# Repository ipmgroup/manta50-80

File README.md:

# manta50-80
Motor-Controller, FOC

### Manta50 key characteristics

    DC-Input 4.4V to 45V 
    Maximum DC / AC (per phase) current - 20A
    Texas Instruments C2000 Piccolo TMS320F28027F
    CAN - MCP2515
    Three-Phase Smart Gate Driver - DRV8305
    one GPIO input for PWM(not supported in FW)

with good cooling in water, you can increase the AC current to 80A. Replacing the resistance from 0.007R to 0.002R.

#### [Firmware](https://github.com/ipmgroup/manta50_fw)

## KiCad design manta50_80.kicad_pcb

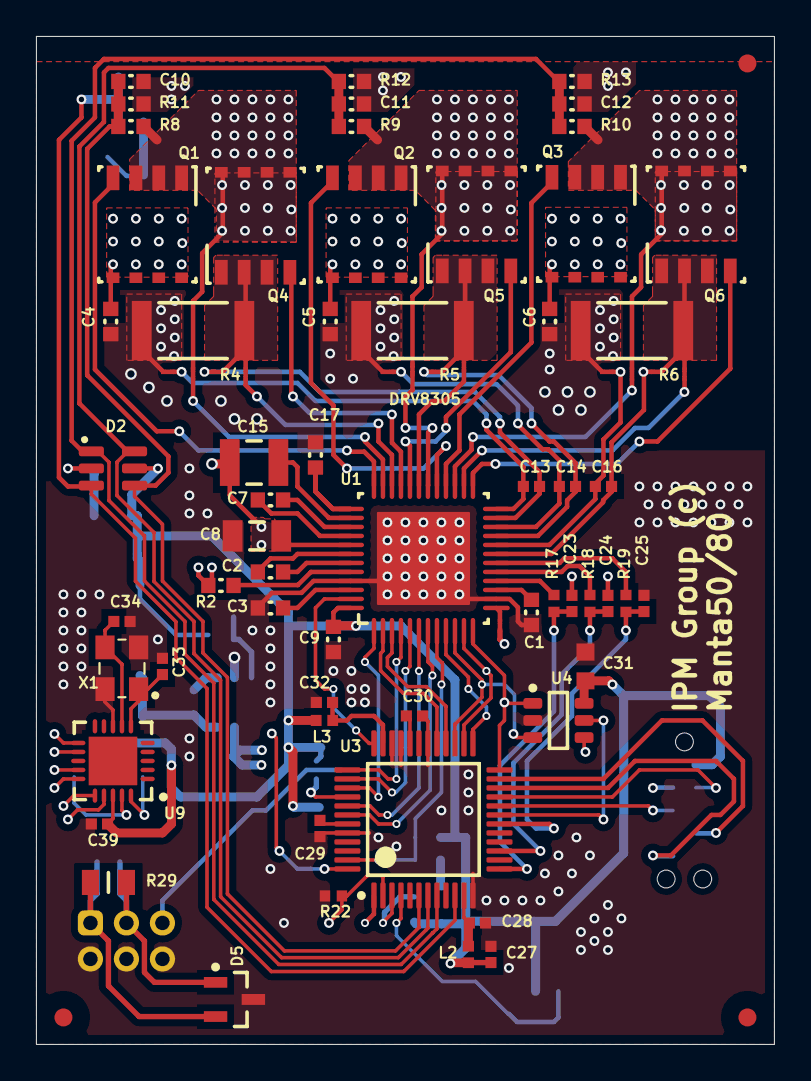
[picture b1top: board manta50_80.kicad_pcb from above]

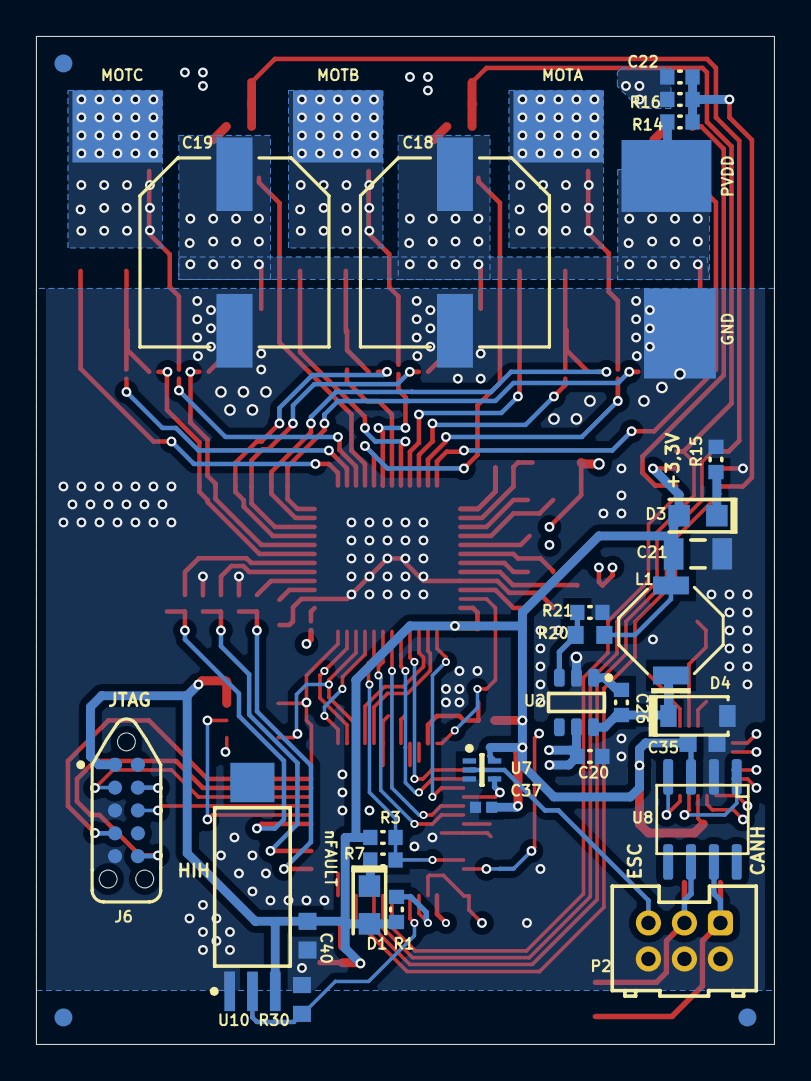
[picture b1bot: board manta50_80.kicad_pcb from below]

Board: 4 copper layers, 41.0 x 56.0 mm, 111 parts (36 on the bottom side), 87 nets.

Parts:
C1, C3, C4, C5, C6, C9, C17, C20: UMK107AB7105KA-T; 0603L
C2, C7: C0603C473K1RACTU; 0603L
C8: GRM31CR71H475KA12L; 1206L
C10, C11, C12, C22: C0603C104J4RACTU; 0603L
C13, C14, C16: 1nF; CAPC1005X55N
C15: GRM32ER72A225KA35L; 1210L
C18, C19: EEE-FT1H331AP; SM_RADIAL_G
C21: GRM31CR71A226KE15L; 1206L
C23, C24, C25: 2.2nF; CAPC1005X55N
C26: GRM188R71C334KA01D; 0603L
C27, C28, C29, C30, C32: 2.2uF; _Users_Public_Documents_Altium_AD15_Library_CernLib_PcbLib_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
C31, C35, C37: 100nF; _Users_Public_Documents_Altium_AD15_Library_CernLib_PcbLib_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
C33, C34: 22pF; CAPC1005X55N
C39: 100nF; CAPC1005X55N
C40: 100nF; _Users_Andrew_Documents_Altium_CernLib_PcbLib_Capacitors SM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
D1: LTST-C170KRKT; LED_LTST-C170
D2: NUP4201MR6T1G; TSOP-6
D3: LTST-C171GKT; LED_LTST-C171
D4: MBR1H100SFT3G; SOD-123FL
D5: SM712; SOT23_N
FID1, FID2, FID3, FID4, FID5, FID6: Fiducial; FIDUCIAL10-20
J1, J2, J3, J4, J5: 2 way net tie junction; J_PIN_4X5
J6: TC2050-IDC-NL-FP; TAG_TC2050-NL
L1: SD53-150-R; SD53
L2: 220R@100MHz; _Users_Public_Documents_Altium_AD15_Library_CernLib_PcbLib_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
L3: 60R@100MHz; _Users_Public_Documents_Altium_AD15_Library_CernLib_PcbLib_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
NT1, NT2, NT3, NT4, NT5, NT6, NT7, NT8, NT9, NT10, NT11, NT12, NT13: Net-Tie; NET-TIE_10MIL
P2: CAN; SHR6_V
Q1, Q2, Q3, Q4, Q5, Q6: CSD18540Q5B; TRANS_NEXFET_Q5B
R1, R3: CRCW060310K0JNEA; 0603L
R2: CRCW0603100RJNEA; 0603L
R4, R5, R6: CRE2512-FZ-R007E-3; 2512L
R7, R15: CRCW0603330RJNEA; 0603L
R8, R9, R10, R14: RC0603FR-0762KL; 0603L
R11, R12, R13, R16: RC0603FR-074K99L; 0603L
R17, R18, R19: 56; RESC1005X40N
R20: 68k; RESC1608X55N
R21: CRCW060320K0FKEA; 0603L
R22: 2k2; _Users_Public_Documents_Altium_AD15_Library_CernLib_PcbLib_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
R29: 120; _Users_Public_Documents_Altium_AD15_Library_CernLib_PcbLib_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
R30: 68k; _Users_Andrew_Documents_Altium_CernLib_PcbLib_Resistors SMD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
U1: DRV8305NPHPQ1; PHP0048G_L
U2: LMR16006XDDC; SOT95P280X110-6N
U3: TMS320F28027F; TSQFP50P900X900X160-48N
U4: 25AA020; SOT95P270X145-6N
U7: SN74LVC1G34DRLR; SOTFL50P160X60-5N
U8: SN65HVD232; SOIC8-N_MC
U9: MCP2515-X/ML; QFN50P400X400X100_HS-21N
U10: HIH-5031; SOT127P1291X295-4N
X1: 16.000MHZ; CRYSTAL-3.2-2.5

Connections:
3.3V: C9.2, C21.1, C27.2, C31.2, C35.2, C37.2, C39.2, C40.2, D1.1, D2.5, D3.1, J6.1, L1.2, L2.2, L3.2, R1.2, R3.2, R20.2, U1.48, U4.6, U7.5, U8.3, U9.18, U10.3
AVDD: C1.2, U1.15
CANH: D5.2, P2.1, R29.1, U8.7
CANL: D5.1, P2.3, R29.2, U8.6
CAN_RX: U8.4, U9.20
CAN_TX: U8.1, U9.19
DVDD: C3.2, U1.46
ECAP1: U3.40, U7.4
EN_GATE: U1.1, U3.39
ESC: P2.5, U7.2
GH_A: Q1.4, U1.36
GH_B: Q2.4, U1.29
GH_C: Q3.4, U1.28
GL_A: Q4.4, U1.33
GL_B: Q5.4, U1.32
GL_C: Q6.4, U1.25
GND: C1.1, C3.1, C4.2, C5.2, C6.2, C8.1, C9.1, C10.2, C11.2, C12.2, C17.1, C18.2, C19.2, C20.2, C21.2, C22.2, C23.1, C24.1, C25.1, C27.1, C28.1, C29.1, C30.1, C31.1, C32.1, C33.1, C34.1, C35.1, C37.1, C39.1, C40.1, D2.2, D4.2, D5.3, J5.1, J6.3, J6.5, NT10.2, NT11.2, NT12.2, P2.2, P2.4, P2.6, R4.1, R5.1, R6.1, R11.1, R12.1, R13.1, R15.1, R16.1, R21.1, R22.1, R30.1, U1.14, U1.45, U1.49, U2.2, U3.12, U3.30, U3.33, U3.34, U3.44, U4.2, U7.3, U8.2, U9.8, U10.1, X1.2, X1.4
HIH: R30.2, U3.4, U10.2
INH_A: U1.2, U3.29
INH_B: U1.4, U3.37
INH_C: U1.6, U3.41
INL_A: U1.3, U3.28
INL_B: U1.5, U3.38
INL_C: U1.7, U3.42
ISEN_A: R17.2, U1.16
ISEN_B: R18.2, U1.17
ISEN_C: R19.2, U1.18
I_A: C23.2, R17.1, U3.13
I_B: C24.2, R18.1, U3.15
I_C: C25.2, R19.1, U3.18
MISO: U1.11, U3.26, U4.4, U9.15
MOSI: U1.10, U3.27, U4.3, U9.14
MOT_A: J1.1, NT1.2, Q1.1, Q1.2, Q1.3, Q4.5, Q4.6, Q4.7, Q4.8, R8.2
MOT_B: J2.1, NT2.2, Q2.1, Q2.2, Q2.3, Q5.5, Q5.6, Q5.7, Q5.8, R9.2
MOT_C: J3.1, NT3.2, Q3.1, Q3.2, Q3.3, Q6.5, Q6.6, Q6.7, Q6.8, R10.2
NCAN_CS: U3.1, U9.16
NCAN_INT: U3.48, U9.11
NFAULT: R3.1, R7.1, U1.8, U3.47
NRESET: NT13.1, R1.1, U3.3, U9.17
NetC2_1: C2.1, U1.43
NetC2_2: C2.2, U1.42
NetC7_1: C7.1, U1.39
NetC7_2: C7.2, U1.40
NetC15_2: C15.2, U1.38
NetC17_2: C17.2, U1.37
NetC26_1: C26.1, D4.1, L1.1, U2.6
NetC26_2: C26.2, U2.1
NetC28_2: C28.2, L2.1, U3.11
NetC29_2: C29.2, U3.43
NetC30_2: C30.2, U3.32
NetC32_2: C32.2, L3.1, U3.35
NetC33_2: C33.2, U9.6, X1.1
NetC34_2: C34.2, U9.7, X1.3
NetD1_2: D1.2, R7.2
NetD3_2: D3.2, R15.2
NetNT4_2: NT4.2, NT7.2, Q4.1, Q4.2, Q4.3, R4.2
NetNT5_2: NT5.2, NT8.2, Q5.1, Q5.2, Q5.3, R5.2
NetNT6_2: NT6.2, NT9.2, Q6.1, Q6.2, Q6.3, R6.2
NetR2_1: R2.1, U1.44
NetR20_1: R20.1, R21.2, U2.3
PVDD: C4.1, C5.1, C6.1, C8.2, C15.1, C18.1, C19.1, C20.1, J4.1, Q1.5, Q1.6, Q1.7, Q1.8, Q2.5, Q2.6, Q2.7, Q2.8, Q3.5, Q3.6, Q3.7, Q3.8, R2.2, R14.2, U1.41, U2.5
PWRGD: NT13.2, U1.13
S1_N: C13.2, NT7.1, U1.23
S1_P: C13.1, NT10.1, U1.24
S2_N: C14.2, NT8.1, U1.21
S2_P: C14.1, NT11.1, U1.22
S3_N: C16.2, NT9.1, U1.19
S3_P: C16.1, NT12.1, U1.20
SCK: U1.12, U3.24, U4.1, U9.12
SCS: U1.9, U3.25
SCS2: U3.19, U4.5
SH_A: NT1.1, U1.35
SH_B: NT2.1, U1.30
SH_C: NT3.1, U1.27
SL_A: NT4.1, U1.34
SL_B: NT5.1, U1.31
SL_C: NT6.1, U1.26
TCK: J6.4, U3.23
TDI: J6.8, U3.20
TDO: J6.6, U3.22
TMS: J6.2, U3.21
TRSTN: J6.9, R22.2, U3.2
VSEN_A: C10.1, D2.4, R8.1, R11.2, U3.6
VSEN_B: C11.1, D2.6, R9.1, R12.2, U3.7
VSEN_C: C12.1, D2.1, R10.1, R13.2, U3.8
VSEN_PVDD: C22.1, D2.3, R14.1, R16.2, U3.10
WAKE: U1.47, U3.36

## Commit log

2023-11-10 add project files
2023-11-10 fix err..
2023-11-11 fix DRC
2023-11-23 Initial comment
2025-01-28 add 3D
2025-01-28 add video
2025-01-28 new video
2025-01-28 add pcb3d
